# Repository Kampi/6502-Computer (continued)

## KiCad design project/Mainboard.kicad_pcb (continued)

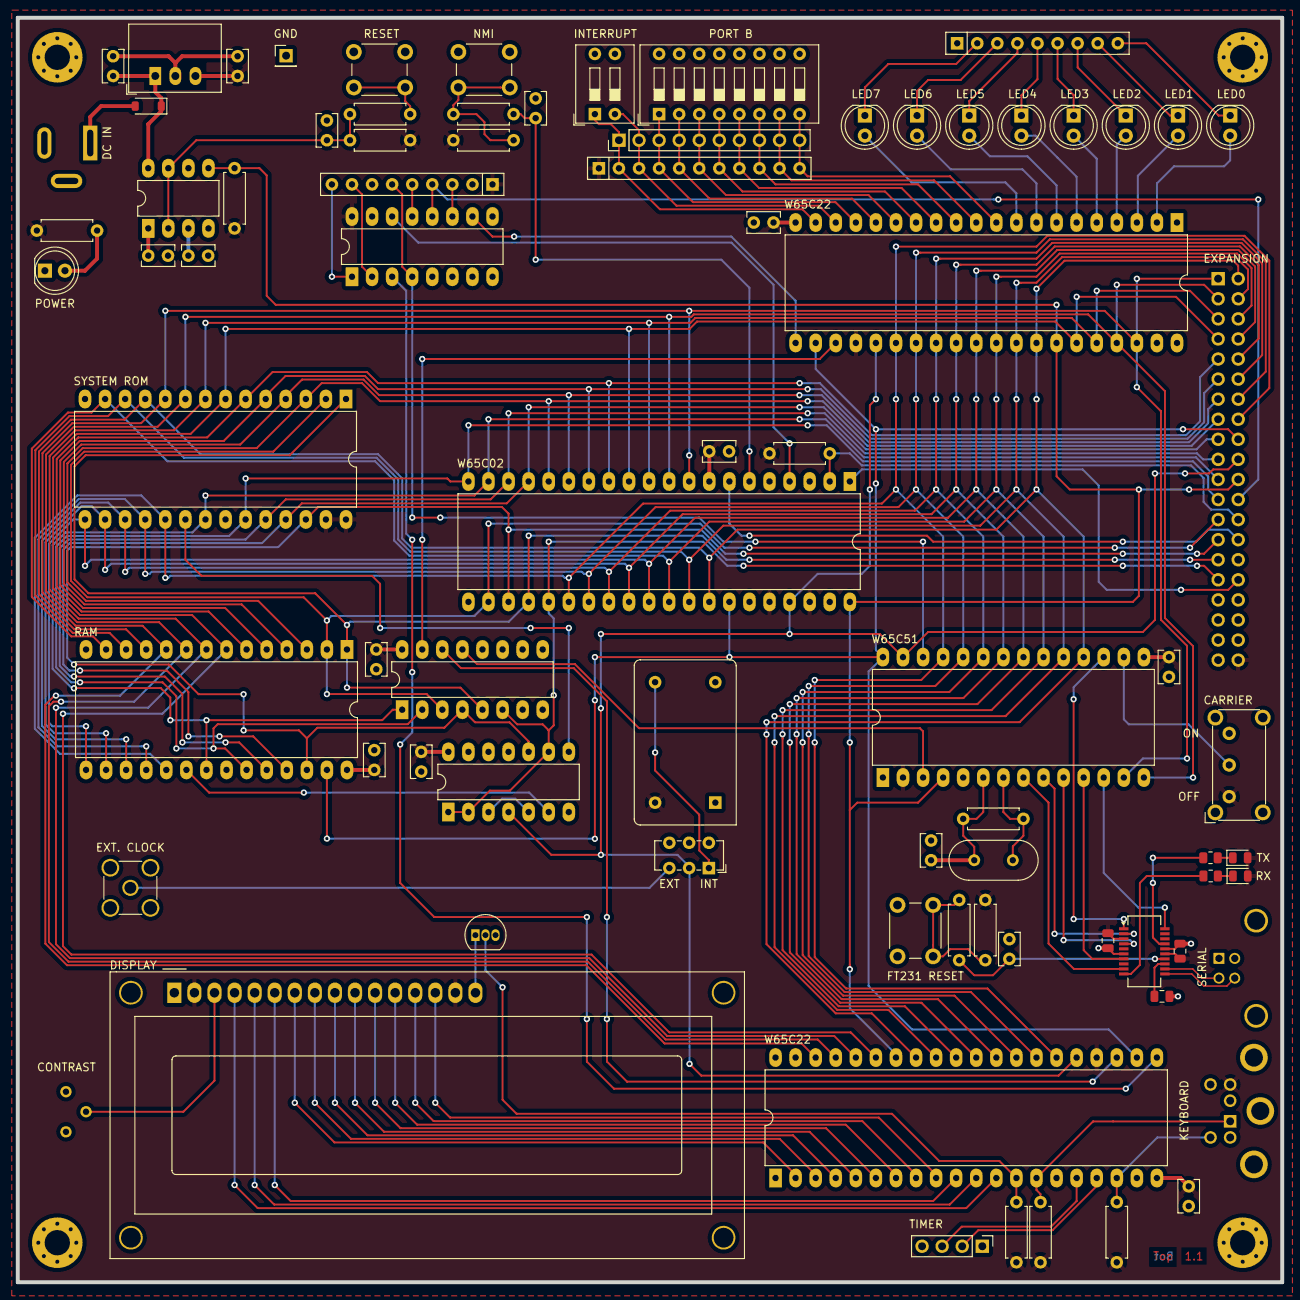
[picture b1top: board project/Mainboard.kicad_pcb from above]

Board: 2 copper layers, 160.0 x 160.0 mm, 80 parts (0 on the bottom side), 120 nets.

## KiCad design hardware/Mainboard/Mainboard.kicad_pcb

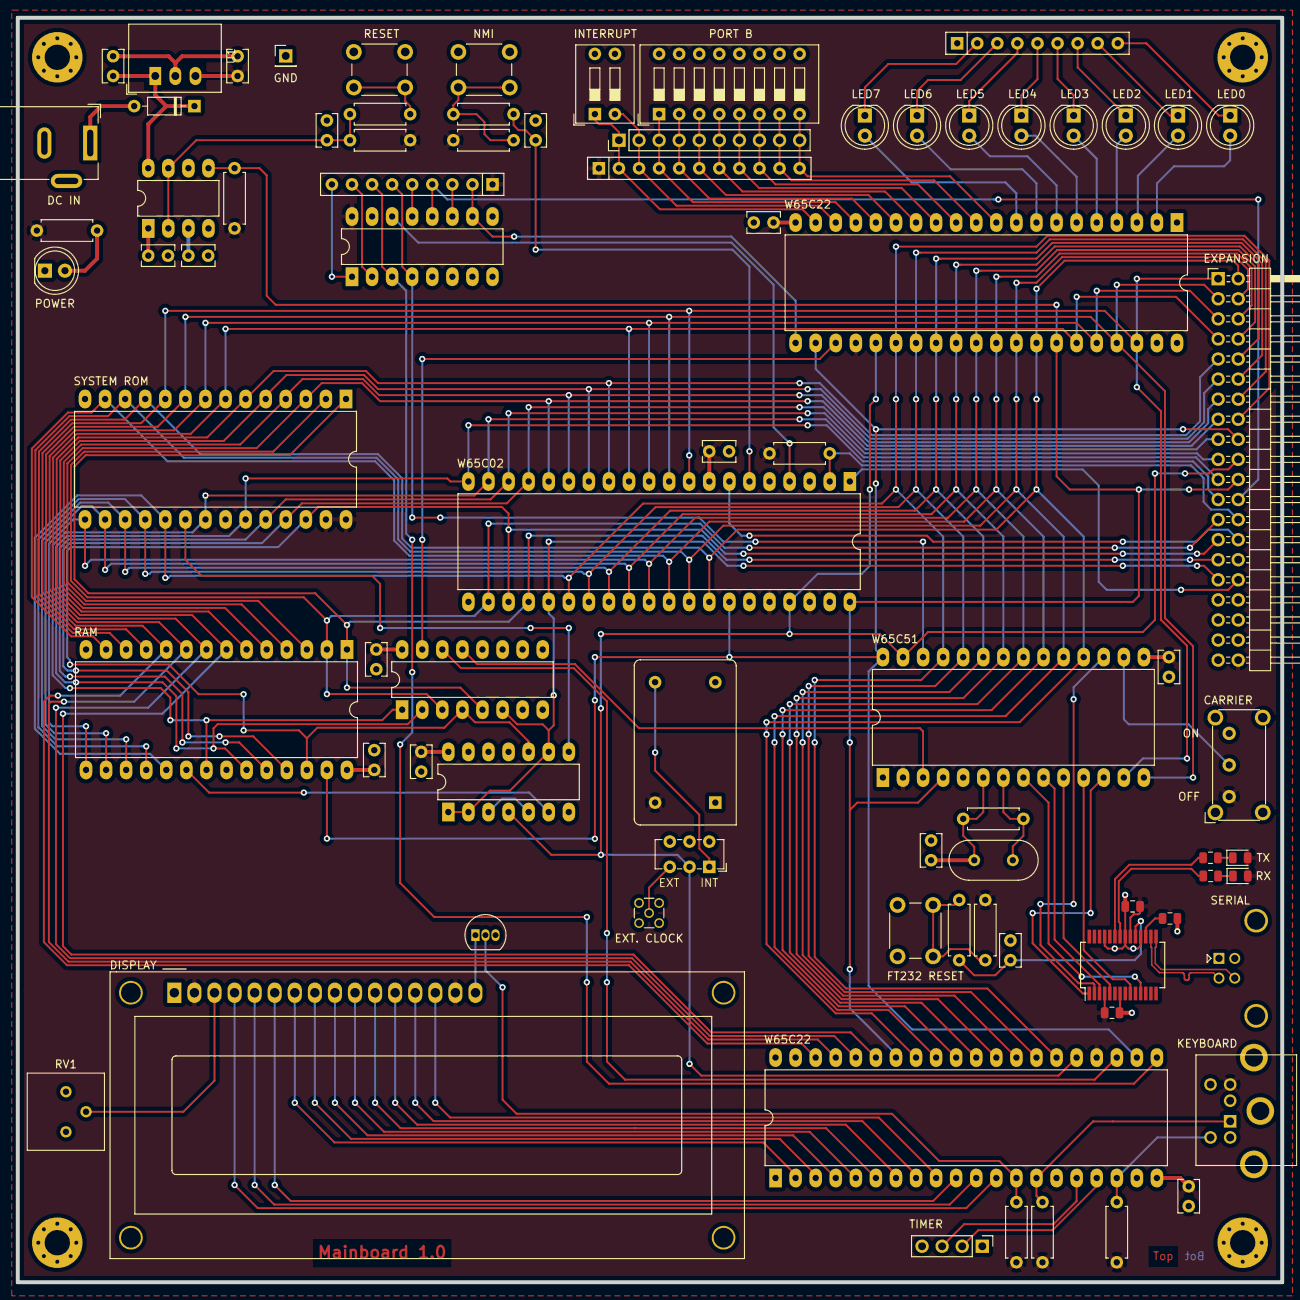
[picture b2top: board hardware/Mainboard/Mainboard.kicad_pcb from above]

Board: 2 copper layers, 160.0 x 160.0 mm, 80 parts (0 on the bottom side), 120 nets.

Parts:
C1, C2, C3, C4, C5, C6, C7, C9, C14, C15, C16, C17, C18: 100nF; C_Rect_L4.0mm_W2.5mm_P2.50mm
C8: 30pF; C_Rect_L4.0mm_W2.5mm_P2.50mm
C10, C11, C12: 100nF; C_0805_2012Metric
C13: 330nF; C_Rect_L4.0mm_W2.5mm_P2.50mm
D1: LED0; LED_D5.0mm
D2: LED1; LED_D5.0mm
D3: LED2; LED_D5.0mm
D4: LED3; LED_D5.0mm
D5: LED4; LED_D5.0mm
D6: LED5; LED_D5.0mm
D7: LED6; LED_D5.0mm
D8: LED7; LED_D5.0mm
D9: TX; LED_0805_2012Metric
D10: RX; LED_0805_2012Metric
D11: 1N4148; D_DO-35_SOD27_P7.62mm_Horizontal
D12: POWER; LED_D5.0mm
DS1: DISPLAY; WC1602A
IC1: 74HC138; DIP-16_W7.62mm_LongPads
IC2: W65C02; DIP-40_W15.24mm_LongPads
IC3: 74HC00; DIP-14_W7.62mm_LongPads
IC4: SYSTEM ROM; DIP-28_W15.24mm_LongPads
IC5, IC7: W65C22; DIP-40_W15.24mm_LongPads
IC6: RAM; DIP-28_W15.24mm_LongPads
IC8: W65C51; DIP-28_W15.24mm_LongPads
IC9: 74HC148; DIP-16_W7.62mm_LongPads
IC10: FT232RL; SSOP-28_5.3x10.2mm_P0.65mm
IC11: TL7702A; DIP-8_W7.62mm_LongPads
R1: 4k7; R_Axial_DIN0207_L6.3mm_D2.5mm_P7.62mm_Horizontal
R2, R3, R4, R6, R10, R11, R13, R15: 10k; R_Axial_DIN0207_L6.3mm_D2.5mm_P7.62mm_Horizontal
R5: 1M; R_Axial_DIN0207_L6.3mm_D2.5mm_P7.62mm_Horizontal
R7, R14: 1k; R_Axial_DIN0207_L6.3mm_D2.5mm_P7.62mm_Horizontal
R8, R9: 1k; R_0805_2012Metric
R12: 470; R_Axial_DIN0207_L6.3mm_D2.5mm_P7.62mm_Horizontal
RN1: 4k7; R_Array_SIP11
RN2: 390; R_Array_SIP9
RN3: 4k7; R_Array_SIP9
RV1: 10k; Bourns_3386P_Vertical
SW1: CARRIER; SW_E-Switch_EG1224_SPDT_Angled
SW2: PORT B; SW_DIP_SPSTx08_Slide_9.78x22.5mm_W7.62mm_P2.54mm
SW3: INTERRUPT; SW_DIP_SPSTx02_Slide_9.78x7.26mm_W7.62mm_P2.54mm
SW4: CLOCK INPUT; SW_E-Switch_EG1271_DPDT
SW5: NMI; SW_PUSH_6mm_H4.3mm
SW6: FT232 RESET; SW_PUSH_6mm_H4.3mm
SW7: RESET; SW_PUSH_6mm_H4.3mm
T1: BC546; TO-92_Inline
U1: R-785.0-1.0; Converter_DCDC_RECOM_R-78E-0.5_THT
X1: PORT B; PinHeader_1x10_P2.54mm_Vertical
X2: EXPANSION; PinHeader_2x20_P2.54mm_Horizontal
X3: TIMER; PinHeader_1x04_P2.54mm_Vertical
X4: KEYBOARD; Mini-DIN_TE_Female_6Pin_2rows
X5: EXT. CLOCK; MMCX_Molex_73415-1471_Vertical
X6: SERIAL; USB-B_TE_2923042_Horizontal
X7: GND; PinHeader_1x01_P2.54mm_Vertical
X8: DC IN; BarrelJack_Wuerth_6941xx301002
XTAL1: 1MHz; Oscillator_DIP-14
XTAL2: 1.8432MHz; Crystal_HC49-U_Vertical

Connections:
+5V: C1.1, C2.1, C3.1, C4.1, C5.1, C6.1, C7.1, C11.1, C12.1, C15.1, D9.2, D10.2, DS1.2, DS1.15, IC1.16, IC2.8, IC2.36, IC2.38, IC3.14, IC4.27, IC4.28, IC5.20, IC5.24, IC6.28, IC7.20, IC7.24, IC8.2, IC8.15, IC9.16, IC10.4, IC10.20, R1.1, R2.1, R3.1, R4.1, R6.1, R10.1, R12.1, R13.1, R15.1, RN1.1, RN3.1, SW1.1, U1.3, X2.40, X4.4, XTAL1.14
+VDC: C13.1, D11.1, IC11.8, U1.1
/IO/A0: IC2.9, IC4.10, IC5.38, IC6.10, IC7.38, IC8.13, X2.1
/IO/A1: IC2.10, IC4.9, IC5.37, IC6.9, IC7.37, IC8.14, X2.3
/IO/A2: IC2.11, IC4.8, IC5.36, IC6.8, IC7.36, X2.5
/IO/A3: IC2.12, IC4.7, IC5.35, IC6.7, IC7.35, X2.7
/IO/A4: IC2.13, IC4.6, IC6.6, X2.9
/IO/A5: IC2.14, IC4.5, IC6.5, X2.11
/IO/A6: IC2.15, IC4.4, IC6.4, X2.13
/IO/A7: IC2.16, IC4.3, IC6.3, X2.15
/IO/A8: IC2.17, IC4.25, IC6.25, X2.17
/IO/A9: IC2.18, IC4.24, IC6.24, X2.19
/IO/A10: IC1.1, IC2.19, IC4.21, IC6.21, X2.21
/IO/A11: IC1.2, IC2.20, IC4.23, IC6.23, X2.23
/IO/A12: IC1.3, IC2.22, IC4.2, IC6.2, X2.25
/IO/A13: IC1.4, IC2.23, IC3.10, IC4.26, IC6.26, X2.27
/IO/A14: IC1.5, IC2.24, IC4.1, IC6.1, X2.29
/IO/A15: IC1.6, IC2.25, IC3.1, IC3.2, IC3.9, X2.31
/IO/CB1: IC7.18, RN1.3, SW3.2, X1.2
/IO/CB2: IC7.19, RN1.2, SW3.1, X1.1
/IO/Clock: IC2.37, IC3.4, IC5.25, IC7.25, IC8.27, SW4.2, X2.20
/IO/D0: IC2.33, IC4.11, IC5.33, IC6.11, IC7.33, IC8.18, X2.2
/IO/D1: IC2.32, IC4.12, IC5.32, IC6.12, IC7.32, IC8.19, X2.4
/IO/D2: IC2.31, IC4.13, IC5.31, IC6.13, IC7.31, IC8.20, X2.6
/IO/D3: IC2.30, IC4.15, IC5.30, IC6.15, IC7.30, IC8.21, X2.8
/IO/D4: IC2.29, IC4.16, IC5.29, IC6.16, IC7.29, IC8.22, X2.10
/IO/D5: IC2.28, IC4.17, IC5.28, IC6.17, IC7.28, IC8.23, X2.12
/IO/D6: IC2.27, IC4.18, IC5.27, IC6.18, IC7.27, IC8.24, X2.14
/IO/D7: IC2.26, IC4.19, IC5.26, IC6.19, IC7.26, IC8.25, X2.16
/IO/PA0: D1.2, IC7.2
/IO/PA1: D2.2, IC7.3
/IO/PA2: D3.2, IC7.4
/IO/PA3: D4.2, IC7.5
/IO/PA4: D5.2, IC7.6
/IO/PA5: D6.2, IC7.7
/IO/PA6: D7.2, IC7.8
/IO/PA7: D8.2, IC7.9
/IO/PB0: IC7.10, RN1.11, SW2.8, X1.10
/IO/PB1: IC7.11, RN1.10, SW2.7, X1.9
/IO/PB2: IC7.12, RN1.9, SW2.6, X1.8
/IO/PB3: IC7.13, RN1.8, SW2.5, X1.7
/IO/PB4: IC7.14, RN1.7, SW2.4, X1.6
/IO/PB5: IC7.15, RN1.6, SW2.3, X1.5
/IO/PB6: IC7.16, RN1.5, SW2.2, X1.4
/IO/PB7: IC7.17, RN1.4, SW2.1, X1.3
/IO/RDY: IC2.2, R4.2, X2.26
/IO/R~W: IC2.34, IC5.22, IC6.27, IC7.22, IC8.28, X2.18
/IO/Sync: IC2.7, X2.28
/IO/~DCD: IC8.16, SW1.2
/IO/~IRQ: IC9.12, RN3.4, X2.24
/IO/~Reset: IC2.40, IC5.34, IC7.34, IC8.4, IC11.5, R15.2, X2.22
/IO/~VP: IC2.1, X2.32
/IRQ/~IRQ_ACIA: IC8.26, IC9.4, RN3.6
/IRQ/~IRQ_CPU: IC2.4, IC9.14
/IRQ/~IRQ_VIA_1: IC7.21, IC9.10, RN3.2
/IRQ/~IRQ_VIA_2: IC5.21, IC9.3, RN3.7
/IRQ/~NMI: C9.1, IC2.6, R7.1
/LCD / PS2/LCD0: DS1.6, IC5.10
/LCD / PS2/LCD1: DS1.5, IC5.11
/LCD / PS2/LCD2: DS1.4, IC5.12
/LCD / PS2/LCD3: DS1.7, IC5.2
/LCD / PS2/LCD4: DS1.8, IC5.3
/LCD / PS2/LCD5: DS1.9, IC5.4
/LCD / PS2/LCD6: DS1.10, IC5.5
/LCD / PS2/LCD7: DS1.11, IC5.6
/LCD / PS2/LCD8: DS1.12, IC5.7
/LCD / PS2/LCD9: DS1.13, IC5.8
/LCD / PS2/LCD10: DS1.14, IC5.9
/LCD / PS2/LCD11: IC5.13, R1.2, T1.2
/LCD / PS2/PS20: IC5.18, R2.2, X4.5
/LCD / PS2/PS21: IC5.14, R3.2, X4.1
/LCD / PS2/Timer0: IC5.17, X3.2
/LCD / PS2/Timer1: IC5.16, X3.3
/Processor/CLOCK_EXT: SW4.3, X5.1
/Processor/CLOCK_INT: SW4.1, XTAL1.8
/Processor/RxD: IC8.12, IC10.1
/Processor/~CS_ACIA: IC1.13, IC8.3
/Processor/~CS_VIA_1: IC1.15, IC7.23
/Processor/~CS_VIA_2: IC1.14, IC5.23
/Processor/~CTS: IC8.9, IC10.3
/Processor/~DSR: IC8.17, IC10.2
/Supply/~Reset_FT232: C14.1, IC10.19, R11.1
/USB/D+: IC10.15, X6.3
/USB/D-: IC10.16, X6.2
/USB/RxD: IC8.10, IC10.5
/USB/~CTS: IC8.8, IC10.11
/USB/~DSR: IC8.11, IC10.9
GND: C1.2, C2.2, C3.2, C4.2, C5.2, C6.2, C7.2, C8.2, C9.2, C10.1, C11.2, C12.2, C13.2, C14.2, C15.2, C16.2, C17.2, C18.2, D12.1, DS1.1, IC1.8, IC2.21, IC3.7, IC4.14, IC4.22, IC5.1, IC6.14, IC6.22, IC7.1, IC8.1, IC9.5, IC9.8, IC10.7, IC10.18, IC10.21, IC10.25, IC11.4, RN2.1, RV1.1, SW1.3, SW2.9, SW2.10, SW2.11, SW2.12, SW2.13, SW2.14, SW2.15, SW2.16, SW3.3, SW3.4, SW5.1, SW6.1, SW7.1, T1.3, U1.2, X2.39, X3.1, X3.4, X4.3, X4.7, X5.2, X6.4, X6.5, X7.1, X8.2, XTAL1.7
unnamed: C8.1, IC8.6, R5.2, XTAL2.1
unnamed: C10.2, IC10.17
unnamed: C16.1, IC11.2, IC11.7, R13.2, R14.1
unnamed: C17.1, IC11.3
unnamed: C18.1, IC11.1
unnamed: D1.1, RN2.9
unnamed: D2.1, RN2.8
unnamed: D3.1, RN2.7
unnamed: D4.1, RN2.6
unnamed: D5.1, RN2.5
unnamed: D6.1, RN2.4
unnamed: D7.1, RN2.3
unnamed: D8.1, RN2.2
unnamed: D9.1, R8.1
unnamed: D10.1, R9.1
unnamed: D11.2, X8.1
unnamed: D12.2, R12.2
unnamed: DS1.3, RV1.2
unnamed: DS1.16, T1.1
unnamed: IC3.3, IC3.5
unnamed: IC3.6, IC6.20
unnamed: IC3.8, IC4.20
unnamed: IC8.7, R5.1, XTAL2.2
unnamed: IC9.1, RN3.9
unnamed: IC9.2, RN3.8
unnamed: IC9.11, RN3.3
unnamed: IC9.13, RN3.5
unnamed: IC10.22, R9.2
unnamed: IC10.23, R8.2
unnamed: R6.2, R7.2, SW5.2
unnamed: R10.2, R11.2, SW6.2
unnamed: R14.2, SW7.2

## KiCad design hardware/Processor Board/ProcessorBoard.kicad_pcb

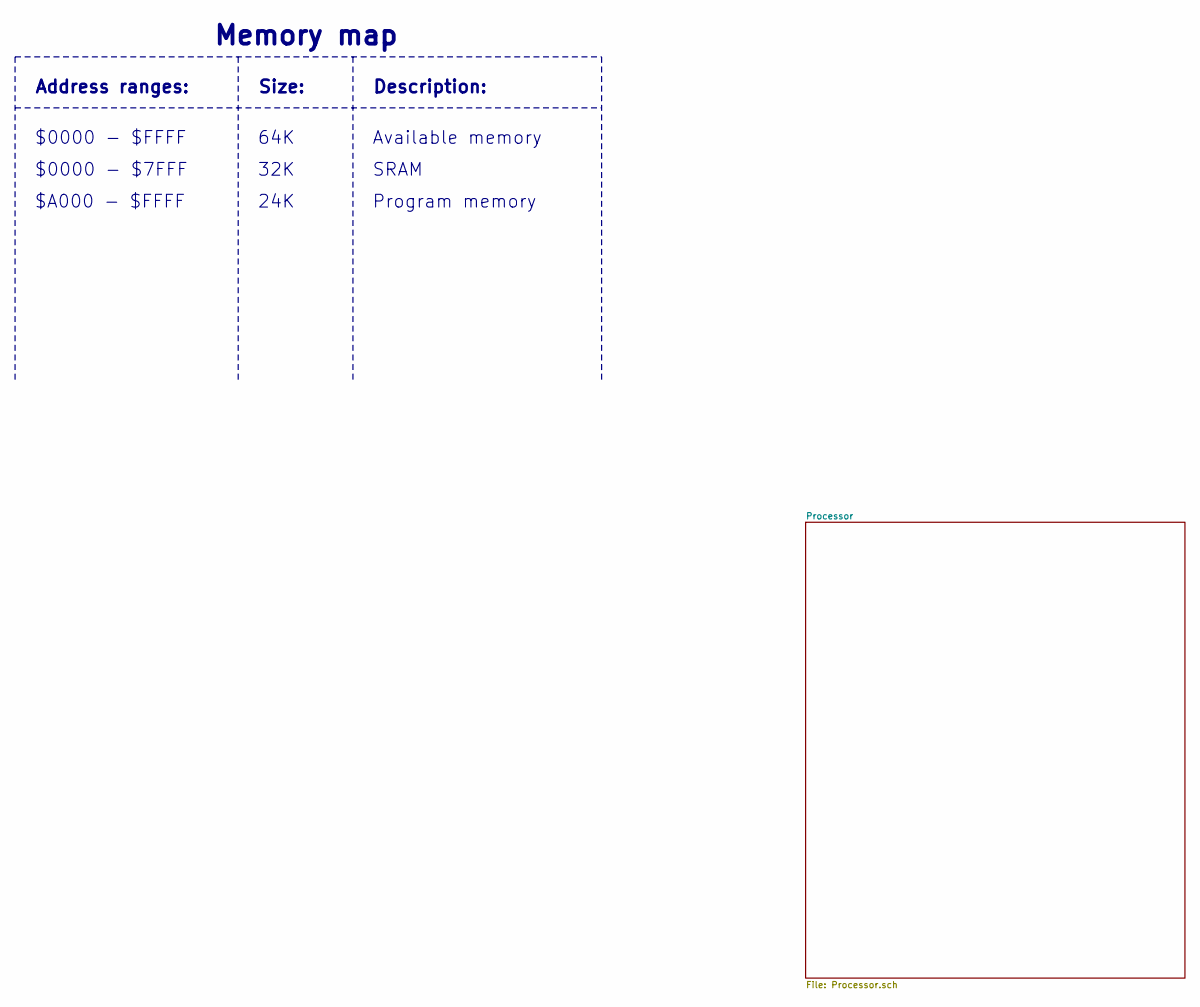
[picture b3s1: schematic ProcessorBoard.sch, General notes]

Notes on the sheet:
Address ranges:
Available memory
Description:
$0000 - $7FFF
SRAM
Memory map
$0000 - $FFFF
Size:
64K
32K
$A000 - $FFFF
24K
Program memory

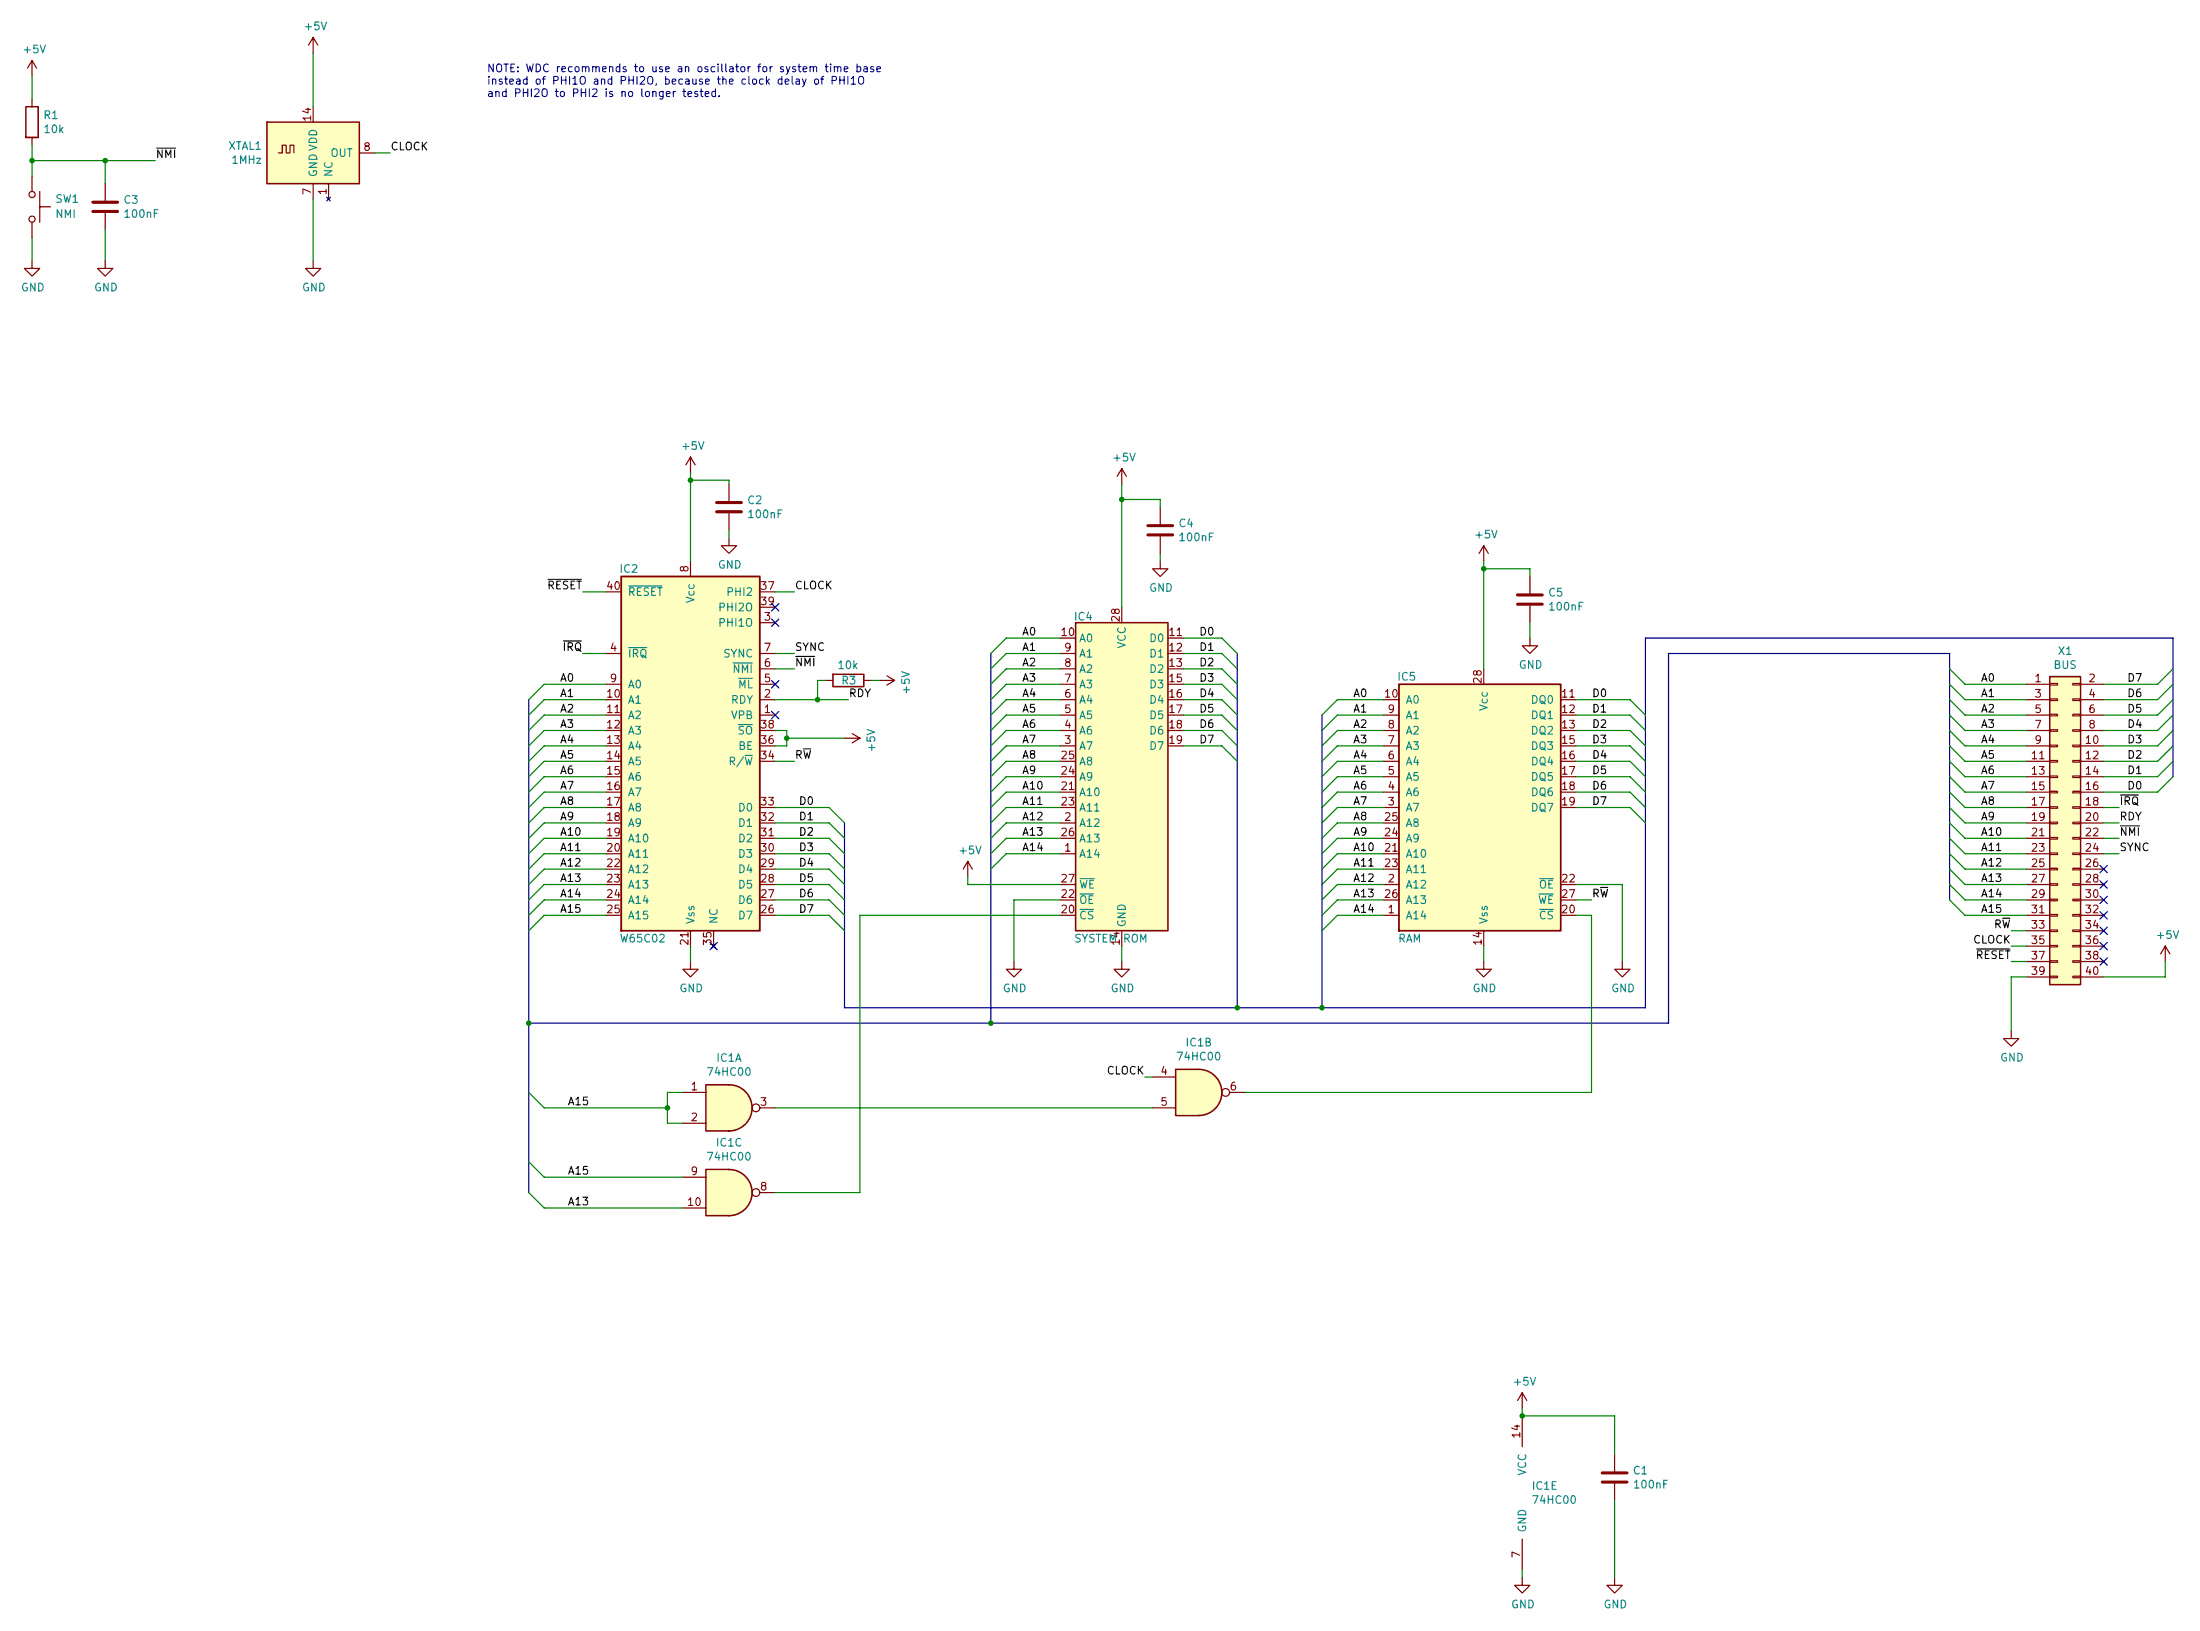
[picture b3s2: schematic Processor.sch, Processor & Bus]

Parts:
C1, C2, C3, C4, C5: 100nF; C_Rect_L4.0mm_W2.5mm_P2.50mm; Mouser 810-FA18X8R1H104KRU6
IC1: 74HC00; DIP-14_W7.62mm_LongPads; Mouser 595-SN74HC00AN
IC2: W65C02; DIP-40_W15.24mm_LongPads; Mouser 955-W65C02S6TPG-14
IC4: SYSTEM ROM; DIP-28_W15.24mm_LongPads; Mouser 556-AT28C256-15PU
IC5: RAM; DIP-28_W15.24mm_LongPads; Mouser 913-AS6C62256-55PCN
R1, R3: 10k; R_Axial_DIN0207_L6.3mm_D2.5mm_P7.62mm_Horizontal; Mouser 603-MFP-25BRD52-10K
SW1: NMI; SW_Tactile_SPST_Angled_PTS645Vx83-2LFS; Mouser 611-PTS645VL832
X1: BUS; PinHeader_2x20_P2.54mm_Horizontal; Mouser 855-M20-9742046
XTAL1: 1MHz; Oscillator_DIP-14; Mouser 520-TCF100-X

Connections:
+5V: C1.1, C2.1, C4.1, C5.1, IC1.14 (VCC), IC2.8 (Vcc), IC2.36 (BE), IC2.38 (~SO), IC4.27 (~WE), IC4.28 (VCC), IC5.28 (Vcc), R1.1, R3.1, X1.40, XTAL1.14 (VDD)
/Processor/A0: IC2.9 (A0), IC4.10 (A0), IC5.10 (A0), X1.1
/Processor/A1: IC2.10 (A1), IC4.9 (A1), IC5.9 (A1), X1.3
/Processor/A2: IC2.11 (A2), IC4.8 (A2), IC5.8 (A2), X1.5
/Processor/A3: IC2.12 (A3), IC4.7 (A3), IC5.7 (A3), X1.7
/Processor/A4: IC2.13 (A4), IC4.6 (A4), IC5.6 (A4), X1.9
/Processor/A5: IC2.14 (A5), IC4.5 (A5), IC5.5 (A5), X1.11
/Processor/A6: IC2.15 (A6), IC4.4 (A6), IC5.4 (A6), X1.13
/Processor/A7: IC2.16 (A7), IC4.3 (A7), IC5.3 (A7), X1.15
/Processor/A8: IC2.17 (A8), IC4.25 (A8), IC5.25 (A8), X1.17
/Processor/A9: IC2.18 (A9), IC4.24 (A9), IC5.24 (A9), X1.19
/Processor/A10: IC2.19 (A10), IC4.21 (A10), IC5.21 (A10), X1.21
/Processor/A11: IC2.20 (A11), IC4.23 (A11), IC5.23 (A11), X1.23
/Processor/A12: IC2.22 (A12), IC4.2 (A12), IC5.2 (A12), X1.25
/Processor/A13: IC1.10, IC2.23 (A13), IC4.26 (A13), IC5.26 (A13), X1.27
/Processor/A14: IC2.24 (A14), IC4.1 (A14), IC5.1 (A14), X1.29
/Processor/A15: IC1.1, IC1.2, IC1.9, IC2.25 (A15), X1.31
/Processor/CLOCK: IC1.4, IC2.37 (PHI2), X1.35, XTAL1.8 (OUT)
/Processor/D0: IC2.33 (D0), IC4.11 (D0), IC5.11 (DQ0), X1.16
/Processor/D1: IC2.32 (D1), IC4.12 (D1), IC5.12 (DQ1), X1.14
/Processor/D2: IC2.31 (D2), IC4.13 (D2), IC5.13 (DQ2), X1.12
/Processor/D3: IC2.30 (D3), IC4.15 (D3), IC5.15 (DQ3), X1.10
/Processor/D4: IC2.29 (D4), IC4.16 (D4), IC5.16 (DQ4), X1.8
/Processor/D5: IC2.28 (D5), IC4.17 (D5), IC5.17 (DQ5), X1.6
/Processor/D6: IC2.27 (D6), IC4.18 (D6), IC5.18 (DQ6), X1.4
/Processor/D7: IC2.26 (D7), IC4.19 (D7), IC5.19 (DQ7), X1.2
/Processor/RDY: IC2.2 (RDY), R3.2, X1.20
/Processor/R~W: IC2.34 (R/~W), IC5.27 (~WE), X1.33
/Processor/SYNC: IC2.7 (SYNC), X1.24
/Processor/~IRQ: IC2.4 (~IRQ), X1.18
/Processor/~NMI: C3.1, IC2.6 (~NMI), R1.2, SW1.1, X1.22
/Processor/~RESET: IC2.40 (~RESET), X1.37
GND: C1.2, C2.2, C3.2, C4.2, C5.2, IC1.7 (GND), IC2.21 (Vss), IC4.14 (GND), IC4.22 (~OE), IC5.14 (Vss), IC5.22 (~OE), SW1.2, X1.39, XTAL1.7 (GND)
unnamed: IC1.3, IC1.5
unnamed: IC1.6, IC5.20 (~CS)
unnamed: IC1.8, IC4.20 (~CS)

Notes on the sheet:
NOTE: WDC recommends to use an oscillator for system time base instead of PHI1O and PHI2O, because the clock delay of PHI1O and PHI2O to PHI2 is no longer tested.

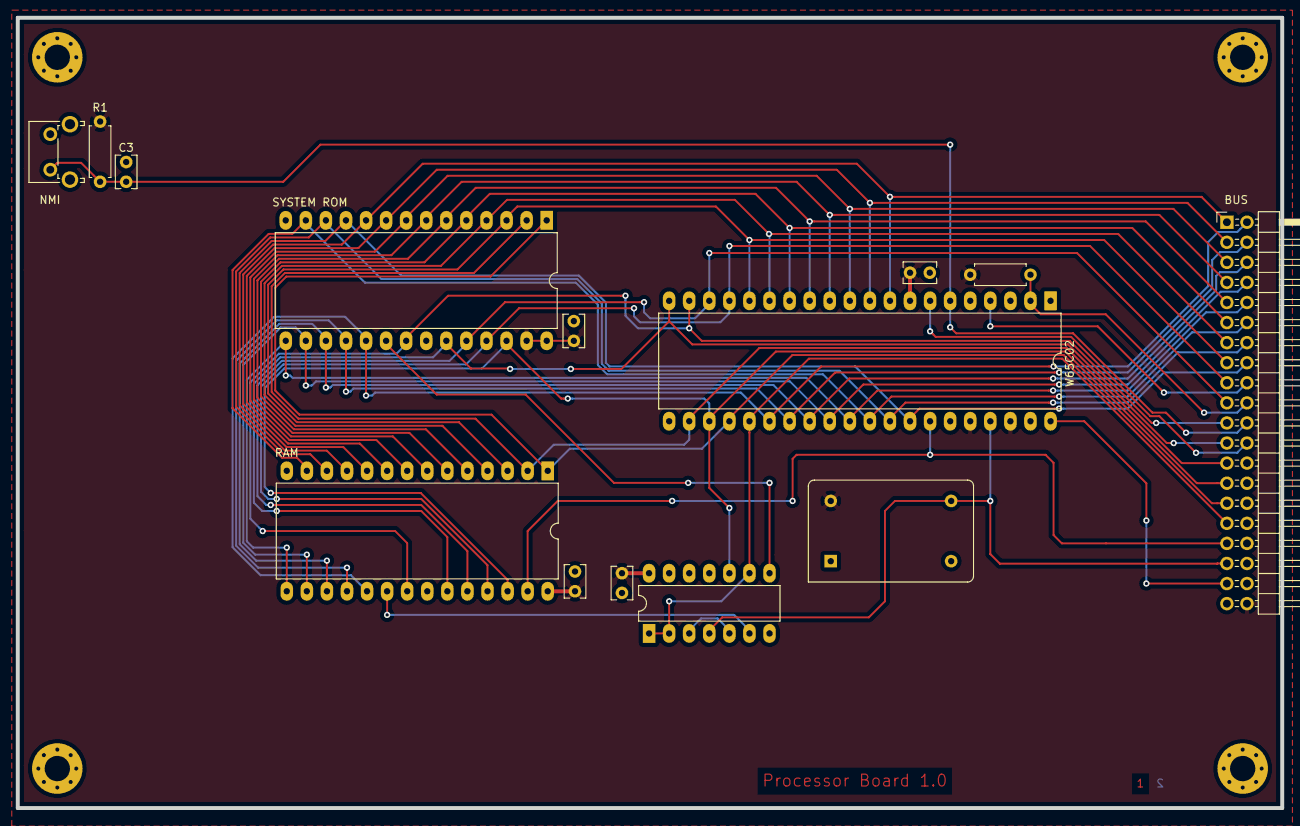
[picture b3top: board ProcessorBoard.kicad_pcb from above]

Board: 2 copper layers, 160.0 x 100.0 mm, 14 parts (0 on the bottom side), 36 nets.

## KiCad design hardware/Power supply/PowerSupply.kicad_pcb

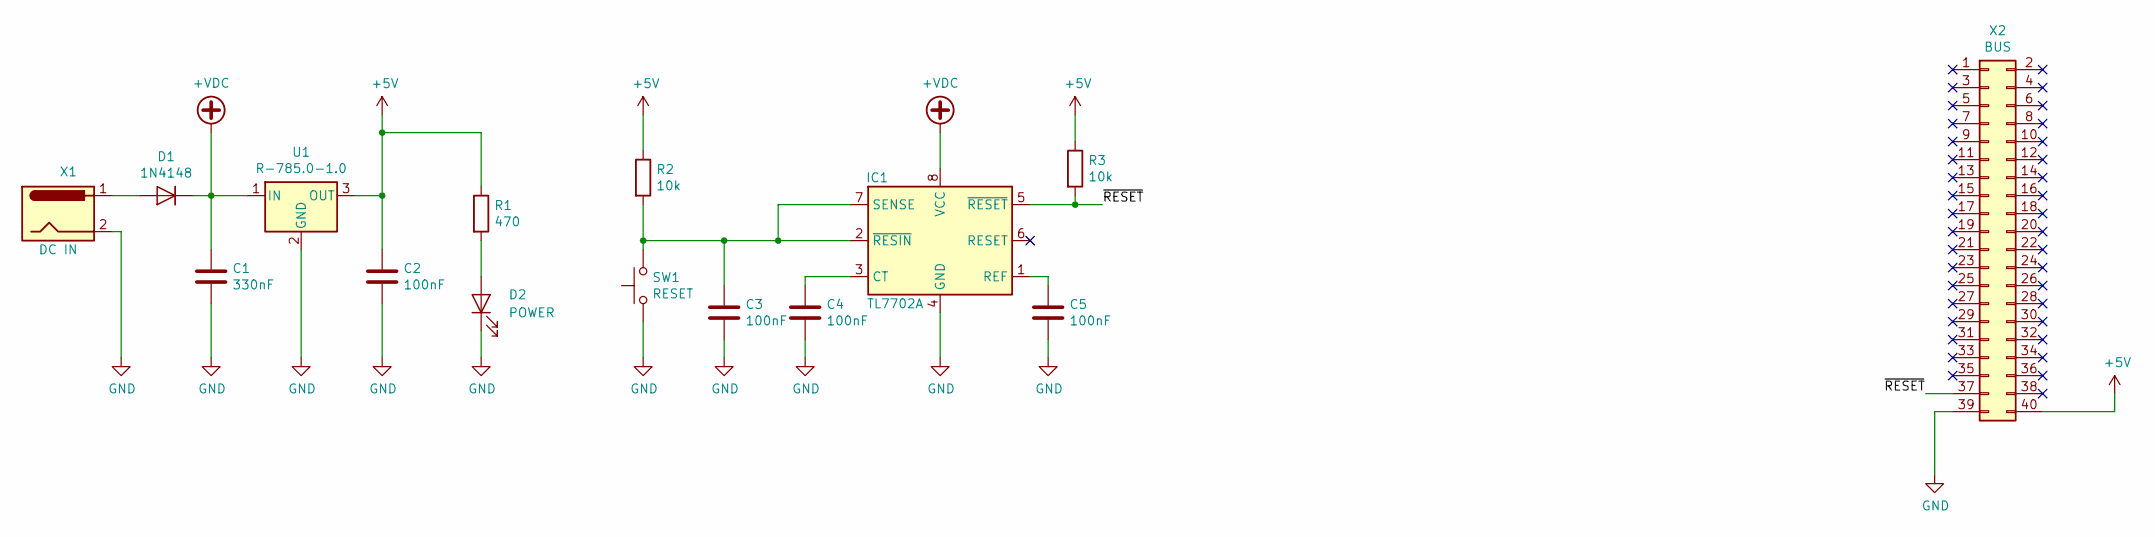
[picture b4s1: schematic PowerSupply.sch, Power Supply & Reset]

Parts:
C1: 330nF; C_Rect_L4.0mm_W2.5mm_P2.50mm; Mouser 581-SR205E334MARTR1
C2, C3, C4, C5: 100nF; C_Rect_L4.0mm_W2.5mm_P2.50mm; Mouser 810-FA18X8R1H104KRU6
D1: 1N4148; D_DO-35_SOD27_P7.62mm_Horizontal; Mouser 512-1N4148
D2: POWER; LED_D5.0mm; Mouser 604-WP73EK/IDA
IC1: TL7702A; DIP-8_W7.62mm_LongPads; Mouser 595-TL7702ACP
R1: 470; R_Axial_DIN0207_L6.3mm_D2.5mm_P7.62mm_Horizontal; Mouser 603-MFP-25BRD52-470R
R2, R3: 10k; R_Axial_DIN0207_L6.3mm_D2.5mm_P7.62mm_Horizontal; Mouser 603-MFP-25BRD52-10K
SW1: RESET; SW_Tactile_SPST_Angled_PTS645Vx83-2LFS; Mouser 611-PTS645VL832
U1: R-785.0-1.0; Converter_DCDC_RECOM_R-78E-0.5_THT; Mouser 919-R-785.0-1.0
X1: DC IN; BarrelJack_Wuerth_6941xx301002; Mouser 710-694106301002
X2: BUS; PinHeader_2x20_P2.54mm_Horizontal; Mouser 855-M20-9742046

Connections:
+5V: C2.1, R1.1, R2.1, R3.1, U1.3 (OUT), X2.40
+VDC: C1.1, D1.1 (K), IC1.8 (VCC), U1.1 (IN)
/~RESET: IC1.5 (~RESET), R3.2, X2.37
GND: C1.2, C2.2, C3.2, C4.2, C5.2, D2.1 (K), IC1.4 (GND), SW1.1, U1.2 (GND), X1.2, X2.39
unnamed: C3.1, IC1.2 (~RESIN), IC1.7 (SENSE), R2.2, SW1.2
unnamed: C4.1, IC1.3 (CT)
unnamed: C5.1, IC1.1 (REF)
unnamed: D1.2 (A), X1.1
unnamed: D2.2 (A), R1.2

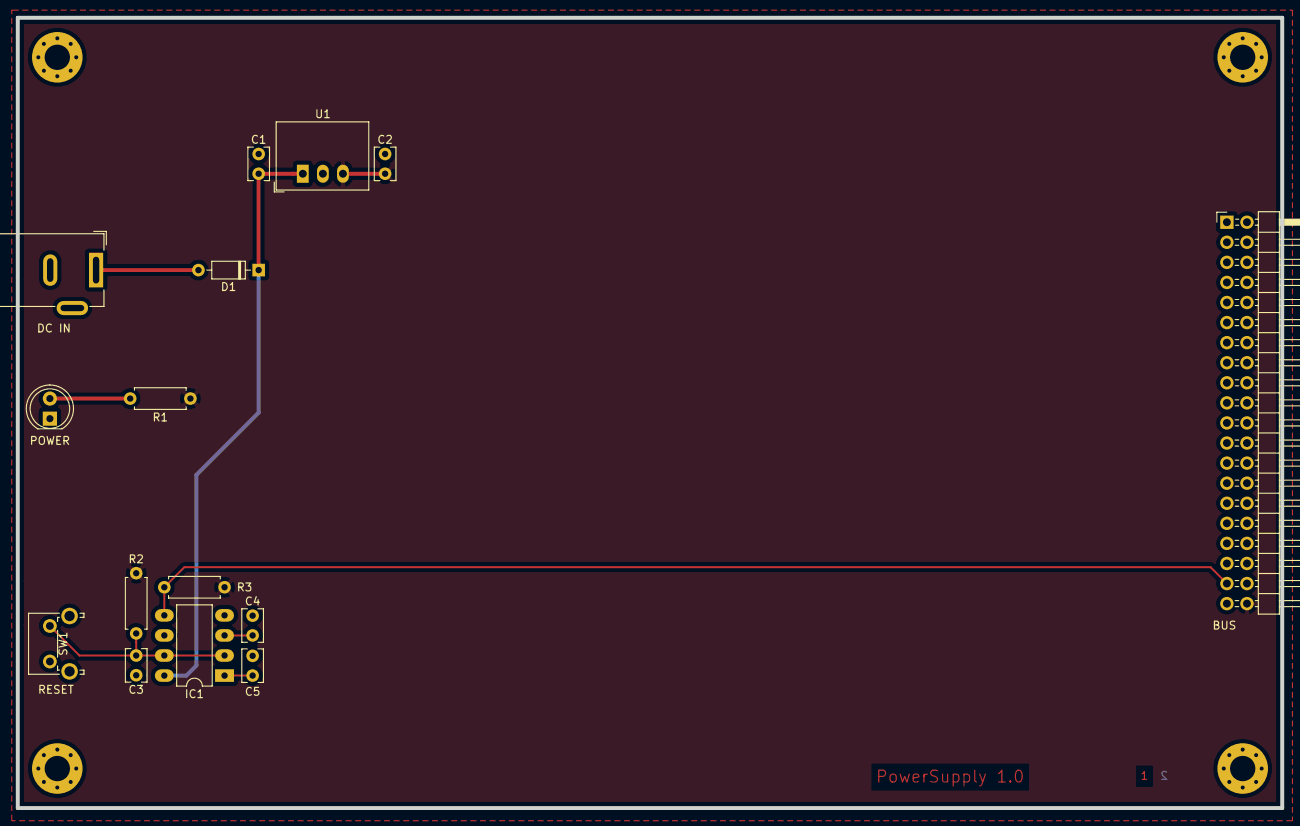
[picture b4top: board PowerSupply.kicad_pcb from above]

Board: 2 copper layers, 160.0 x 100.0 mm, 15 parts (0 on the bottom side), 9 nets.
